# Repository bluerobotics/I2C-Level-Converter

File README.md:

# I2C-Level-Converter
Simple I2C Level Converter with Dronecode compatible connectors.

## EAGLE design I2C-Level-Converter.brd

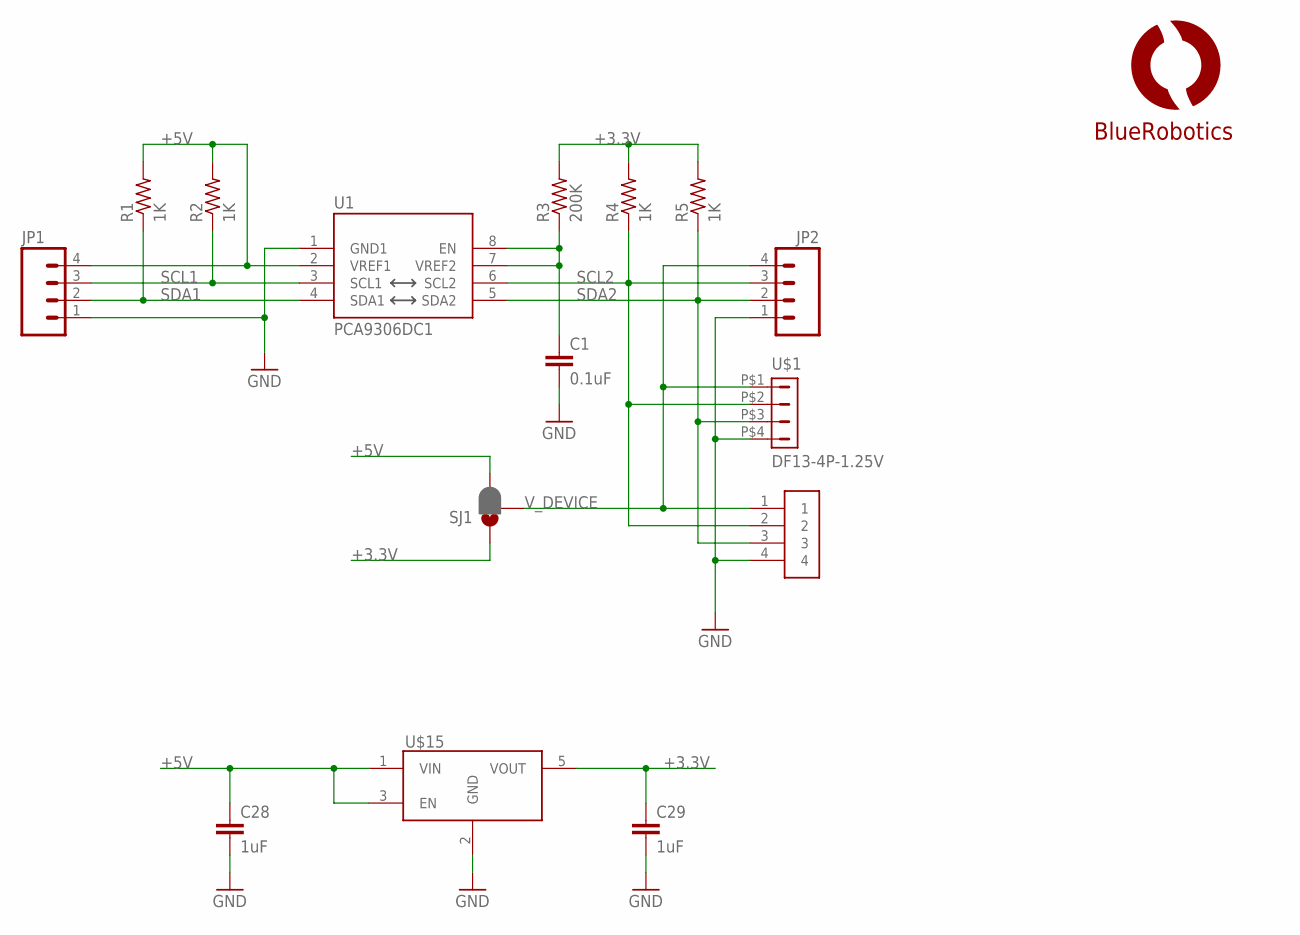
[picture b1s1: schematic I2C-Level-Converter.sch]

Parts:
C1: 0.1uF; C0603
C28, C29: 1uF; 0603-CAP
JP1, JP2: M04PTH; 1X04
R1, R2, R4, R5: 1K; R0603
R3: 200K; R0603
SJ1: JUMPER-PAD-3-2OF3_NC_BY_PASTE; PAD-JUMPER-3-2OF3_NC_BY_PASTE_YES_SILK_FULL_BOX
U1: PCA9306DC1; PSOP-8
U$1: DF13-4P-1.25V; DF13C-4P-1.25V
U$2: JST-GH-4SMT; JST-GH-TOP-4
U$3: LOGOBR-LOGO-S; BR-LOGO-SMALL
U$15: VREG-MIC5365; SC70-5L

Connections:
+3.3V: C29.1, R3.2, R4.2, R5.2, SJ1.1, U$15.5 (VOUT)
+5V: C28.1, JP1.4, R1.2, R2.2, SJ1.3, U1.2 (VREF1), U$15.1 (VIN), U$15.3 (EN)
GND: C1.2, C28.2, C29.2, JP1.1, JP2.1, U1.1 (GND1), U$1.P$4 (4), U$2.4, U$15.2 (GND)
unnamed: C1.1, R3.1, U1.7 (VREF2), U1.8 (EN)
SCL1: JP1.3, R2.1, U1.3 (SCL1)
SCL2: JP2.3, R4.1, U1.6 (SCL2), U$1.P$2 (2), U$2.2
SDA1: JP1.2, R1.1, U1.4 (SDA1)
SDA2: JP2.2, R5.1, U1.5 (SDA2), U$1.P$3 (3), U$2.3
V_DEVICE: JP2.4, SJ1.2, U$1.P$1 (1), U$2.1

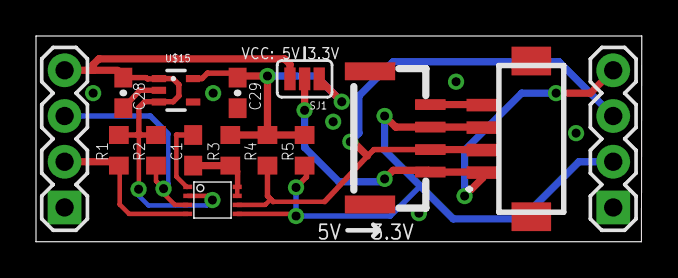
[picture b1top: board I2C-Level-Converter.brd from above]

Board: 2 copper layers, 33.7 x 11.4 mm, 16 parts (1 on the bottom side), 9 nets.

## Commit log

2016-11-16 Added PDF, Schematic, and Board Layout

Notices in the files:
parts and their libraries:
SparkFun-Passives: Licensing: Creative Commons ShareAlike 4.0 International - https://creativecommons.org/licenses/by-sa/4.0
